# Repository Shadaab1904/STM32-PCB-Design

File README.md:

# STM32-PCB-Design
KiCad project:  STM32 PCB Design on STM32F103C8T6

# About
This repository contains the KiCad 9.0 schematic for a custom-designed STM32-based development board. The board is built around the **STM32F103C8T6** microcontroller and provides core functionalities such as USB power, external clocking, GPIO headers, voltage regulation, and indicator LEDs ideal for prototyping, embedded systems development.

It includes: 

- STM32F103C8T6:  ARM Cortex-M3 microcontroller (Blue Pill)     
- USB_B_Micro: USB Micro-B connector for programming/power    
- AMS1117-3.3: Voltage regulator (3.3V output)                
- Crystal: External crystal oscillator with GND pads     
- FB: FerriteBead: Noise filter on power rail
- LED: Status or debug indicator
- Resistor: For LED and pull-up/down functions
- Capacitor: Decoupling and oscillator loading
- Conn_01x04_Pin: 4-pin GPIO header                            
- MountingHoles: Mechanical support for enclosure/PCB mount   

## 📂 Project structure
- `My_STM32_Board.kicad_sch` – Schematic file
- `My_STM32_Board_pcb` – PCB layout file
- `My_STM32_Board_pro` – KiCad project file
- `gerber/` – Gerber and drill files for fabrication
- `bom.csv` – Bill of Materials

- ## ⚙️ Tools
- Designed with [KiCad](https://kicad.org/)

- ## Features
  
- **Input**: USB Micro-B (5V)
- **Regulation**: 5V to 3.3V via **AMS1117-3.3** LDO regulator
- **Noise Filtering**: Ferrite bead between 3.3V rail and microcontroller

  Clock Circuit:

- Onboard Crystal oscillator provides accurate timing
- Crystal is connected to STM32’s OSC_IN/OSC_OUT with matching capacitors

  I/O and Connectivity:

- **USB Connector** allows firmware upload and power
- **4-pin GPIO Header** for serial comms, I2C/SPI, or digital I/O
- **LED Indicator** for debug or power status
- 

- ## 📦 Fabrication
Use the files in the `gerber/` directory to order PCBs from manufacturers (e.g., JLCPCB etc.).

- ## 📄 License
MIT License – feel free to modify and use.

## 🙌 Contributions
Pull requests welcome! If you spot issues or have improvements, please open an issue or PR.

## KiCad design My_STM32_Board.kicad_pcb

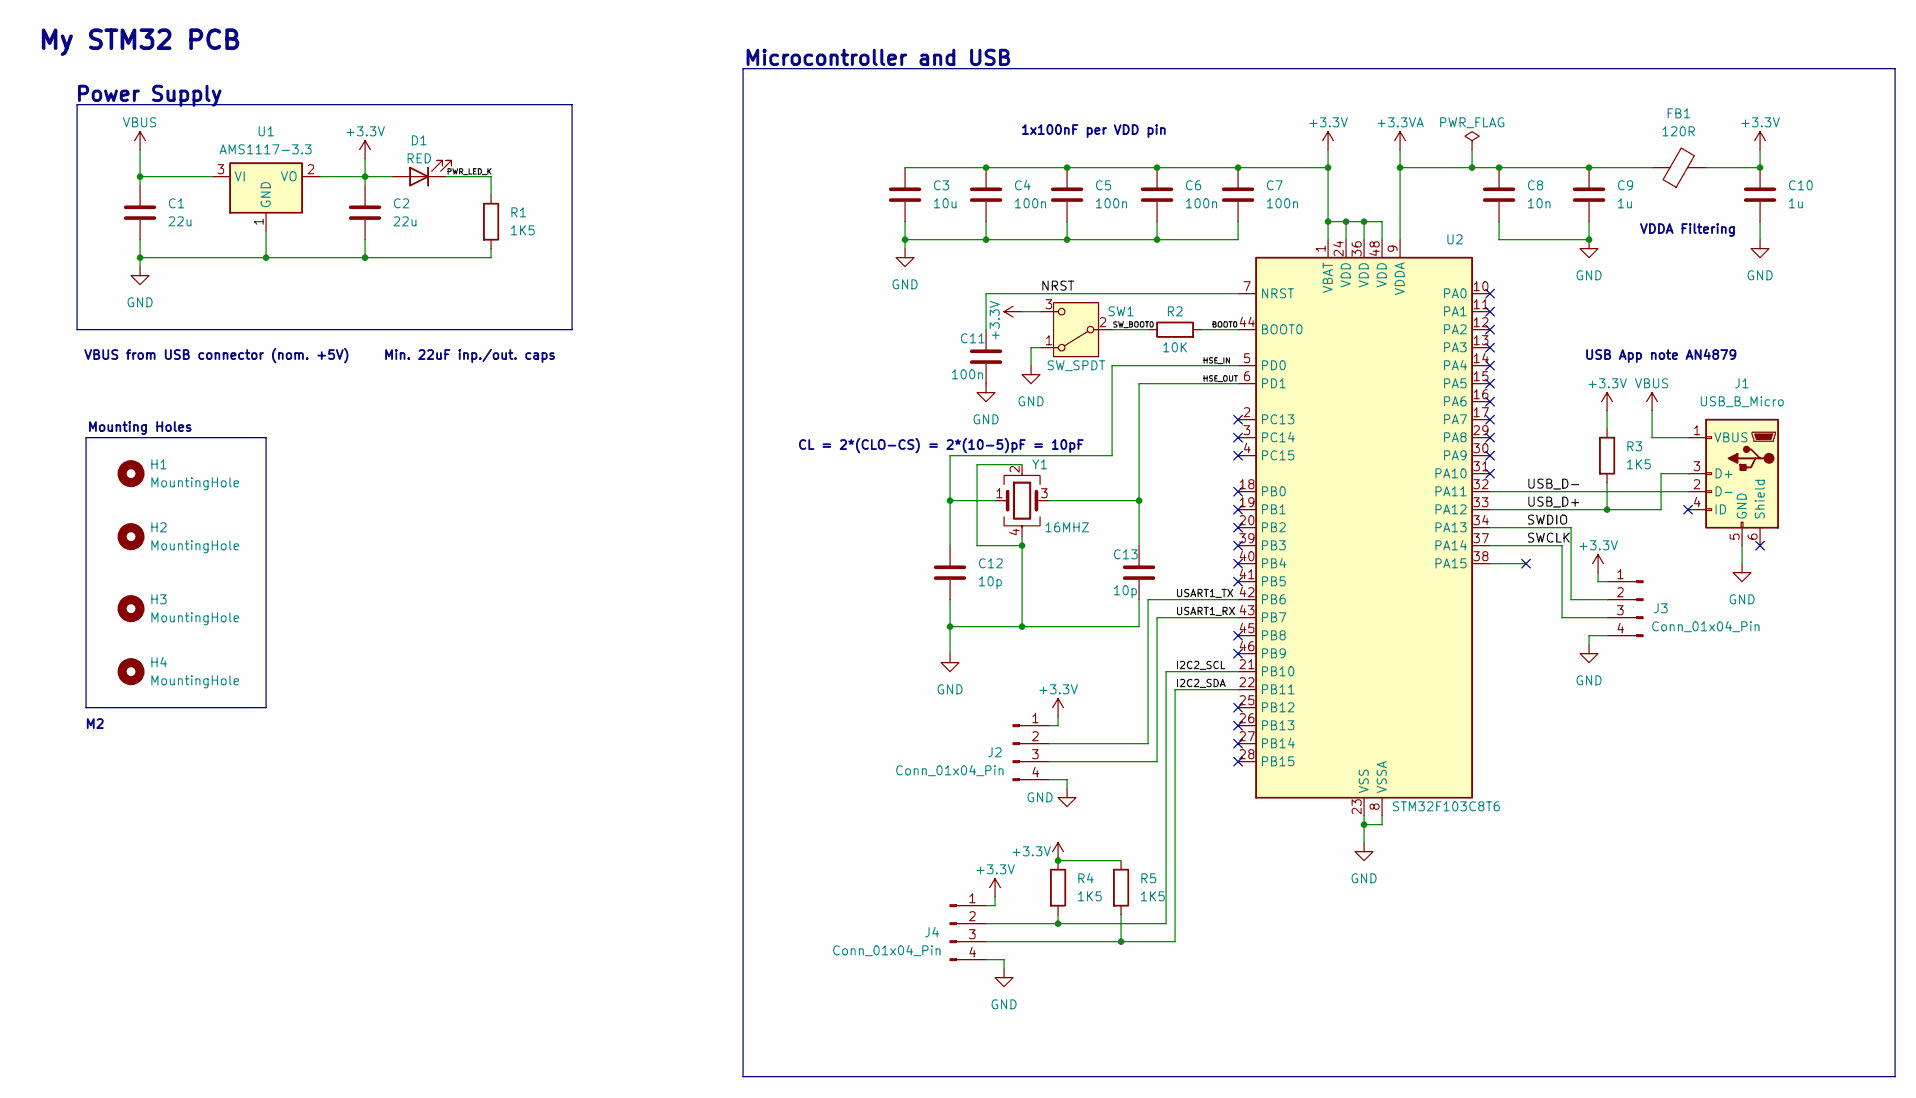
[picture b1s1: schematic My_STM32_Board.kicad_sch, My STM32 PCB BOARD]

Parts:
C1, C2: 22u; C_0805_2012Metric
C3: 10u; C_0603_1608Metric
C4, C5, C6, C7, C11: 100n; C_0402_1005Metric
C8: 10n; C_0402_1005Metric
C9, C10: 1u; C_0402_1005Metric
C12, C13: 10p; C_0402_1005Metric
D1: RED; LED_0603_1608Metric
FB1: 120R; L_0603_1608Metric
H1, H2, H3, H4: MountingHole; MountingHole_2.2mm_M2
J1: USB_B_Micro; USB_Micro-B_Wuerth_629105150521
J2, J3, J4: Conn_01x04_Pin; PinHeader_1x04_P2.54mm_Vertical
R1, R3, R4, R5: 1K5; R_0402_1005Metric
R2: 10K; R_0402_1005Metric
SW1: SW_SPDT; SW_SPDT_PCM12
U1: AMS1117-3.3; SOT-223-3_TabPin2
U2: STM32F103C8T6; LQFP-48_7x7mm_P0.5mm
Y1: 16MHZ; Crystal_SMD_3225-4Pin_3.2x2.5mm

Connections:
+3.3V: C2.1, C3.1, C4.1, C5.1, C6.1, C7.1, C10.1, D1.2 (A), FB1.2, J2.1, J3.1, J4.1, R3.1, R4.1, R5.1, SW1.3 (C), U1.2 (VO), U2.1 (VBAT), U2.24 (VDD), U2.36 (VDD), U2.48 (VDD); also elsewhere on the board
+3.3VA: C8.1, C9.1, FB1.1, U2.9 (VDDA)
/BOOT0: R2.2, U2.44 (BOOT0)
/HSE_IN: C12.1, U2.5 (PD0), Y1.1
/HSE_OUT: C13.1, U2.6 (PD1), Y1.3
/I2C2_SCL: J4.2, R4.2, U2.21 (PB10)
/I2C2_SDA: J4.3, R5.2, U2.22 (PB11)
/NRST: C11.1, U2.7 (NRST)
/PWR_LED_K: D1.1 (K), R1.1
/SWCLK: J3.3, U2.37 (PA14)
/SWDIO: J3.2, U2.34 (PA13)
/SW_BOOT0: R2.1, SW1.2 (B); also elsewhere on the board
/USART1_RX: J2.3, U2.43 (PB7)
/USART1_TX: J2.2, U2.42 (PB6)
/USB_D+: J1.3 (D+), R3.2, U2.33 (PA12)
/USB_D-: J1.2 (D-), U2.32 (PA11)
GND: C1.2, C2.2, C3.2, C4.2, C5.2, C6.2, C7.2, C8.2, C9.2, C10.2, C11.2, C12.2, C13.2, J1.5 (GND), J2.4, J3.4, J4.4, R1.2, SW1.1 (A), U1.1 (GND), U2.8 (VSSA), U2.23 (VSS), U2.35 (VSS), U2.47 (VSS), Y1.2, Y1.4; also elsewhere on the board
VBUS: C1.1, J1.1 (VBUS), U1.3 (VI)

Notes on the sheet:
Power Supply
1x100nF per VDD pin
Microcontroller and USB
USB App note AN4879
VDDA Filtering
VBUS from USB connector (nom. +5V) Min. 22uF inp./out. caps
Mounting Holes
My STM32 PCB
CL = 2*(CLO-CS) = 2*(10-5)pF = 10pF

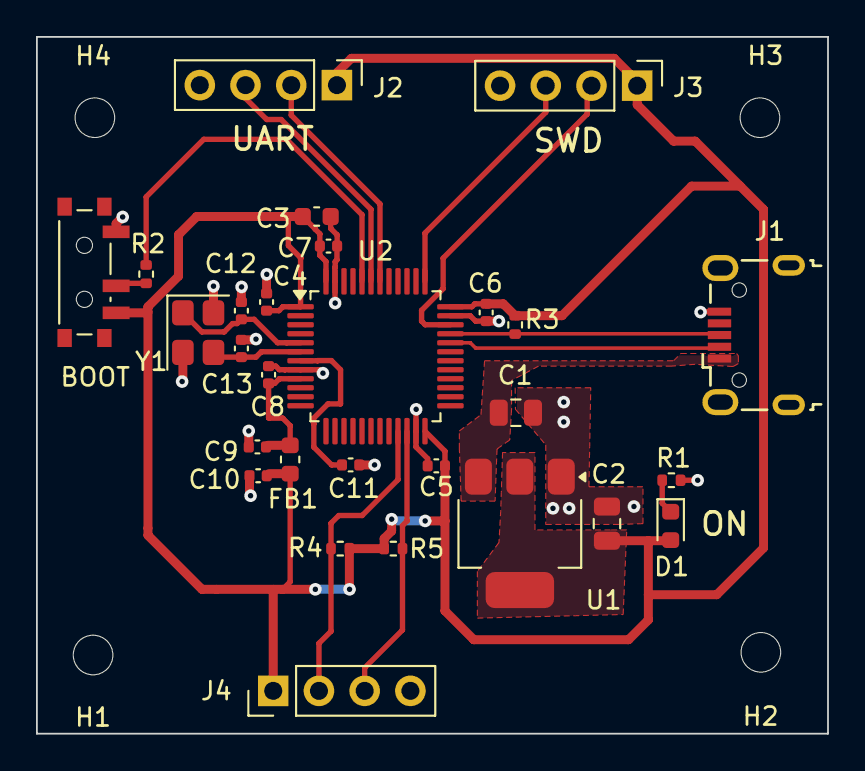
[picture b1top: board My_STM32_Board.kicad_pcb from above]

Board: 2 copper layers, 44.0 x 38.7 mm, 32 parts (0 on the bottom side), 18 nets.

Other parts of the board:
BOOT: SW_SPDT; SW_SPDT_PCM12

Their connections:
+3.3V: BOOT.3 (C); also elsewhere on the board
/SW_BOOT0: BOOT.2 (B); also elsewhere on the board
GND: BOOT.1 (A); also elsewhere on the board

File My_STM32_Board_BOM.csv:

Reference,Qty,Value,DNP,Exclude from BOM,Exclude from Board,Footprint,Datasheet
"C1,C2",2,22u,,,,Capacitor_SMD:C_0805_2012Metric,~
C3,1,10u,,,,Capacitor_SMD:C_0603_1608Metric,~
"C4,C5,C6,C7,C11",5,100n,,,,Capacitor_SMD:C_0402_1005Metric,~
C8,1,10n,,,,Capacitor_SMD:C_0402_1005Metric,~
"C9,C10",2,1u,,,,Capacitor_SMD:C_0402_1005Metric,~
"C12,C13",2,10p,,,,Capacitor_SMD:C_0402_1005Metric,~
D1,1,RED,,,,LED_SMD:LED_0603_1608Metric,~
FB1,1,120R,,,,Inductor_SMD:L_0603_1608Metric,~
"H1,H2,H3,H4",4,MountingHole,,Excluded from BOM,,MountingHole:MountingHole_2.2mm_M2,~
J1,1,USB_B_Micro,,,,Connector_USB:USB_Micro-B_Wuerth_629105150521,~
"J2,J3,J4",3,Conn_01x04_Pin,,,,Connector_PinHeader_2.54mm:PinHeader_1x04_P2.54mm_Vertical,~
"R1,R3,R4,R5",4,1K5,,,,Resistor_SMD:R_0402_1005Metric,~
R2,1,10K,,,,Resistor_SMD:R_0402_1005Metric,~
SW1,1,SW_SPDT,,,,Button_Switch_SMD:SW_SPDT_PCM12,~
U1,1,AMS1117-3.3,,,,Package_TO_SOT_SMD:SOT-223-3_TabPin2,http://www.advanced-monolithic.com/pdf/ds1117.pdf
U2,1,STM32F103C8T6,,,,Package_QFP:LQFP-48_7x7mm_P0.5mm,https://www.st.com/resource/en/datasheet/stm32f103c8.pdf
Y1,1,16MHZ,,,,Crystal:Crystal_SMD_3225-4Pin_3.2x2.5mm,~

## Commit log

2025-07-20 Create Docs
2025-07-20 Create temp
